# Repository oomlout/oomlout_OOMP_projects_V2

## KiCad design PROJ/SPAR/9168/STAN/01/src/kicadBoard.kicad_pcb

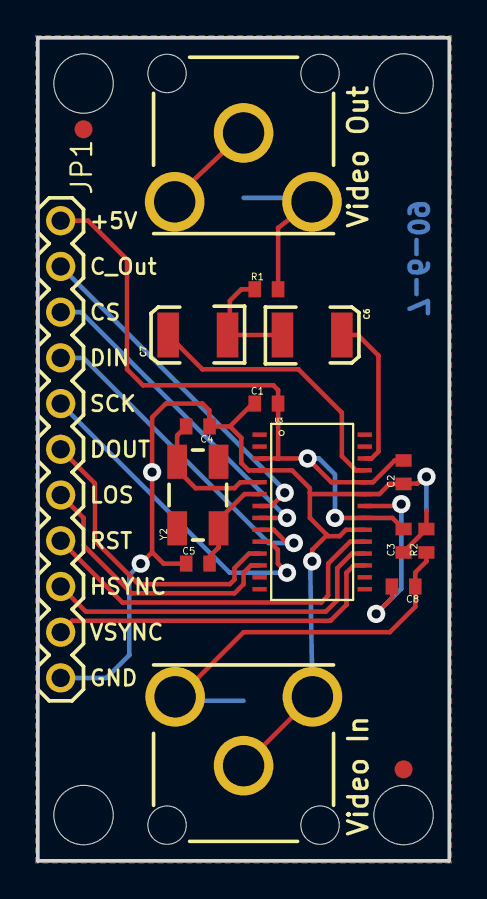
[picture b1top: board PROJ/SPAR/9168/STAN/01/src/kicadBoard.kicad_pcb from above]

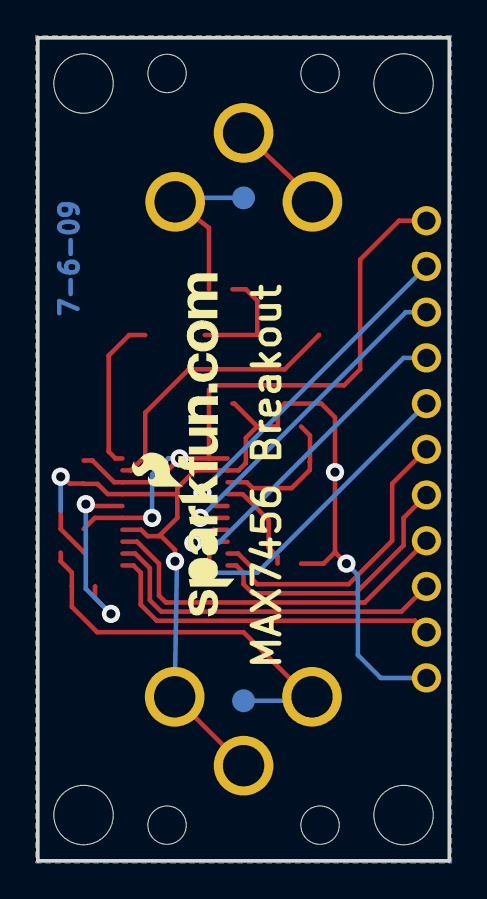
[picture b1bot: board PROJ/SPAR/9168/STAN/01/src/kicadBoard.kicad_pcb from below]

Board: 2 copper layers, 22.9 x 45.7 mm, 24 parts (3 on the bottom side), 19 nets.

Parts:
C1, C2, C3, C8: 0.1uF; C0402
C4, C5: 22pf; C0402
C6, C7: 47uF; EIA3528
J1, J2: POWER_JACKRCA_LOCK; RCA_LOCK
JP1: M11PTH; 1X11
R1, R2: 75; C0402
U3: MAX7456; TSSOP28
U$2, U$12, U$13, U$14: STAND-OFF
U$8: LOGO-SFENEW; SFE-NEW-WEBLOGO
U$9, U$10: FIDUCIAL1X2; FIDUCIAL-1X2
V_IN0: TEST-POINT3X5; PAD.03X.05
V_OUT0: TEST-POINT3X5; PAD.03X.05
Y2: 27MHz; CRYSTAL-SMD-5X3

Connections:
5V: C1.2, C2.2, C3.2, JP1.1, U3.3, U3.21, U3.24
CLKOUT: JP1.2, U3.7
DIN: JP1.4, U3.9
DOUT: JP1.6, U3.11
GND: C1.1, C2.1, C3.1, C4.1, C5.1, J1.BARREL, J1.SPRING, J2.BARREL, J2.SPRING, JP1.11, R2.2, U3.4, U3.20, U3.23
LOS: JP1.7, U3.12
unnamed: C4.2, U3.5, Y2.3
unnamed: C5.2, U3.6, Y2.1
unnamed: C6.C, C7.C, R1.1
unnamed: C7.A, U3.25
unnamed: C6.A, U3.26
unnamed: J1.BREAK, R1.2, V_OUT0.P$1
unnamed: C8.2, U3.22
unnamed: C8.1, J2.BREAK, R2.1, V_IN0.P$1
RESET: JP1.8, U3.19
SCK: JP1.5, U3.10
~CS: JP1.3, U3.8
~HSYNC: JP1.9, U3.18
~VSYNC: JP1.10, U3.17

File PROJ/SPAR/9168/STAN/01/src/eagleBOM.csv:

"Part";"Value";"Device";"Package";"Description";"";
"C1";"0.1uF";"CAP0402";"C0402";"Capacitor";"";
"C2";"0.1uF";"CAP0402";"C0402";"Capacitor";"";
"C3";"0.1uF";"CAP0402";"C0402";"Capacitor";"";
"C4";"22pf";"CAP0402";"C0402";"Capacitor";"";
"C5";"22pf";"CAP0402";"C0402";"Capacitor";"";
"C6";"47uF";"CAP_POL3528";"EIA3528";"Capacitor Polarized";"";
"C7";"47uF";"CAP_POL3528";"EIA3528";"Capacitor Polarized";"";
"C8";"0.1uF";"CAP0402";"C0402";"Capacitor";"";
"J1";"POWER_JACKRCA_LOCK";"POWER_JACKRCA_LOCK";"RCA_LOCK";"Power Jack";"";
"J2";"POWER_JACKRCA_LOCK";"POWER_JACKRCA_LOCK";"RCA_LOCK";"Power Jack";"";
"JP1";"M11PTH";"M11PTH";"1X11";"Header 11";"";
"R1";"75";"RESISTOR0402";"C0402";"Resistor";"";
"R2";"75";"RESISTOR0402";"C0402";"Resistor";"";
"U$2";"STAND-OFF";"STAND-OFF";"STAND-OFF";"Stand Off";"";
"U$8";"LOGO-SFENEW";"LOGO-SFENEW";"SFE-NEW-WEBLOGO";"Spark Fun Electronics PCB Logo";"";
"U$9";"FIDUCIAL1X2";"FIDUCIAL1X2";"FIDUCIAL-1X2";"Fiducial Alignment Points";"";
"U$10";"FIDUCIAL1X2";"FIDUCIAL1X2";"FIDUCIAL-1X2";"Fiducial Alignment Points";"";
"U$12";"STAND-OFF";"STAND-OFF";"STAND-OFF";"Stand Off";"";
"U$13";"STAND-OFF";"STAND-OFF";"STAND-OFF";"Stand Off";"";
"U$14";"STAND-OFF";"STAND-OFF";"STAND-OFF";"Stand Off";"";
"U3";"MAX7456";"MAX7456";"TSSOP28";"";"";
"V_IN";"TEST-POINT3X5";"TEST-POINT3X5";"PAD.03X.05";"";"";
"V_OUT";"TEST-POINT3X5";"TEST-POINT3X5";"PAD.03X.05";"";"";
"Y2";"27MHz";"CRYSTAL5X3";"CRYSTAL-SMD-5X3";"Crystals";"";

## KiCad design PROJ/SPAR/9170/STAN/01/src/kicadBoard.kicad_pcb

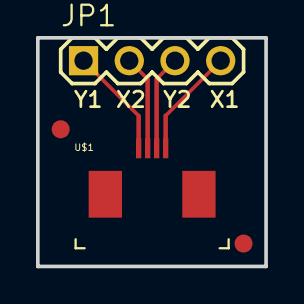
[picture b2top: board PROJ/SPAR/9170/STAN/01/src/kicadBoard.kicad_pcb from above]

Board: 16 copper layers, 12.7 x 12.7 mm, 5 parts (1 on the bottom side), 4 nets.

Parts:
FID1, FID2: FIDUCIAL1X2; FIDUCIAL-1X2
JP1: 1X04
U$1: DS_TOUCH_CONNECTOR
U$2: LOGO-SFESK; SFE-LOGO-FLAME

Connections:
unnamed: JP1.4, U$1.X1
unnamed: JP1.3, U$1.Y2
unnamed: JP1.2, U$1.X2
unnamed: JP1.1, U$1.Y1

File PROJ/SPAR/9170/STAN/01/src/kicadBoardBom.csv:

"Id";"Designator";"Package";"Quantity";"Designation";"Supplier and ref";
1;"JP1";"1X04";1;"";;;
2;"FID2,FID1";"FIDUCIAL-1X2";2;"FIDUCIAL1X2";;;
3;"U$1";"DS_TOUCH_CONNECTOR";1;"DS_TOUCH_CONNECTOR";;;
4;"U$2";"SFE-LOGO-FLAME";1;"LOGO-SFESK";;;

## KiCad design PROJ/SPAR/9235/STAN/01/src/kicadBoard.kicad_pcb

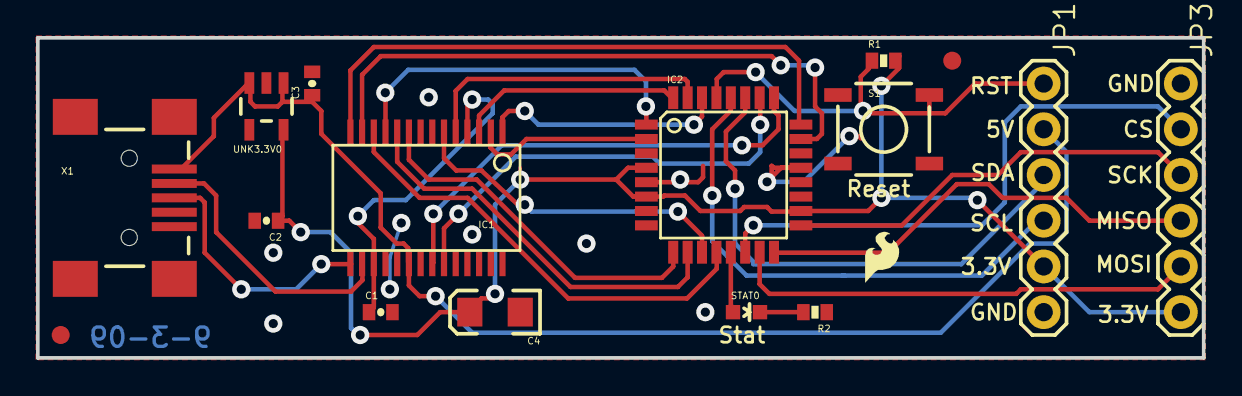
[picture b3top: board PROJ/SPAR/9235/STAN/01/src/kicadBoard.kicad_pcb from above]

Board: 2 copper layers, 64.8 x 17.8 mm, 18 parts (1 on the bottom side), 28 nets.

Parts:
C1, C2: 0.1u; 0402-CAP
C3: 10n; 0402-CAP
C4: 10u; EIA3216
IC1: FT245RL; SSOP28DB
IC2: ATMEGA168; TQFP32-08
JP1, JP3: 1X06
R1: 10k; 0402-RES
R2: 330; 0402-RES
S1: TACTILE_SWITCH_SMD
STAT0: RED; LED-0603
U$3: LOGO-SFENEW; SFE-NEW-WEBLOGO
U$5, U$6: FIDUCIAL1X2; FIDUCIAL-1X2
U$7: LOGO-SFESK; SFE-LOGO-FLAME
UNK3.3V0: V_REG_LDOSMD; SOT23-5
X1: USBSMD; USB-MINIB

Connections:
3.3V: C2.1, C4.A, IC2.4, IC2.6, IC2.18, JP1.5, JP3.6, R1.2, UNK3.3V0.5
CS: IC2.14, JP3.2
GND: C1.2, C2.2, C3.2, C4.C, IC1.7, IC1.18, IC1.21, IC1.25, IC1.26, IC2.3, IC2.5, IC2.21, JP1.6, JP3.1, R2.1, S1.4, UNK3.3V0.2, X1.GND
IOVDD: C1.1, IC1.4, IC1.17
MISO: IC2.16, JP3.4
MOSI: IC2.15, JP3.5
unnamed: IC1.1, IC2.30
unnamed: IC1.5, IC2.31
unnamed: IC1.3, IC2.32
unnamed: IC1.11, IC2.1
unnamed: IC1.2, IC2.2
unnamed: IC1.9, IC2.9
unnamed: IC1.10, IC2.10
unnamed: IC1.6, IC2.11
unnamed: IC1.23, IC2.26
unnamed: IC1.16, X1.D-
unnamed: IC1.15, X1.D+
unnamed: IC1.22, IC2.25
unnamed: IC1.14, IC2.24
unnamed: IC1.13, IC2.23
unnamed: IC1.12, IC2.12
unnamed: IC2.13, STAT0.A
unnamed: R2.2, STAT0.C
RESET: IC2.29, JP1.1, R1.1, S1.2
SCK: IC2.17, JP3.3
SCL: IC2.28, JP1.4
SDA: IC2.27, JP1.3
VUSB: C3.1, IC1.20, JP1.2, UNK3.3V0.1, UNK3.3V0.3, X1.VBUS

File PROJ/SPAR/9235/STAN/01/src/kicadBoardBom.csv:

"Id";"Designator";"Package";"Quantity";"Designation";"Supplier and ref";
1;"R1";"0402-RES";1;"10k";;;
2;"C1,C2";"0402-CAP";2;"0.1u";;;
3;"UNK3.3V0";"SOT23-5";1;"V_REG_LDOSMD";;;
4;"STAT0";"LED-0603";1;"RED";;;
5;"JP3,JP1";"1X06";2;"";;;
6;"U$7";"SFE-LOGO-FLAME";1;"LOGO-SFESK";;;
7;"IC1";"SSOP28DB";1;"FT245RL";;;
8;"U$6,U$5";"FIDUCIAL-1X2";2;"FIDUCIAL1X2";;;
9;"C3";"0402-CAP";1;"10n";;;
10;"R2";"0402-RES";1;"330";;;
11;"C4";"EIA3216";1;"10u";;;
12;"S1";"TACTILE_SWITCH_SMD";1;"";;;
13;"IC2";"TQFP32-08";1;"ATMEGA168";;;
14;"X1";"USB-MINIB";1;"USBSMD";;;
15;"U$3";"SFE-NEW-WEBLOGO";1;"LOGO-SFENEW";;;

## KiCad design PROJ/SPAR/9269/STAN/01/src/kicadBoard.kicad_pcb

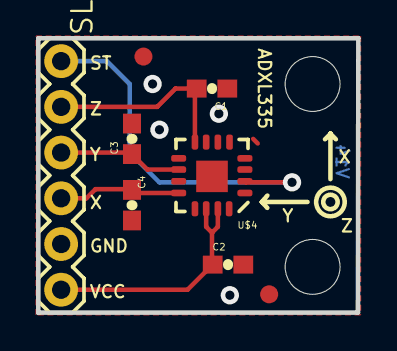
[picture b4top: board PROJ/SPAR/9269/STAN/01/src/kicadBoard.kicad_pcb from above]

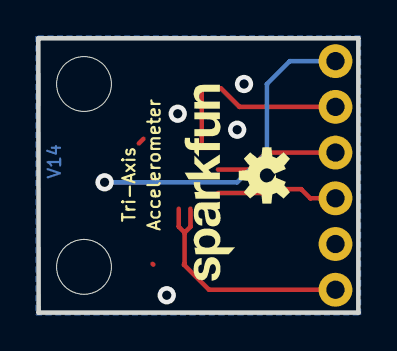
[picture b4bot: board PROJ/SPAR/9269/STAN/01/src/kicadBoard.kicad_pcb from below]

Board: 16 copper layers, 17.8 x 15.2 mm, 12 parts (2 on the bottom side), 6 nets.

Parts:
C1, C2, C3, C4: 0.1uF; 0603-CAP
SL1: 1X06
U$1, U$3: FIDUCIAL1X2; FIDUCIAL-1X2
U$4: ADXL335-PATRICK""; ADXL335-P
U$5: OSHW-LOGO-S
U$6, U$7: STAND-OFF-TIGHT
U$8: SFE_LOGO_NAME_.1

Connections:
GND: C1.1, C2.2, C3.2, C4.2, SL1.5, U$4.3, U$4.5, U$4.6, U$4.7
ST: SL1.1, U$4.2
VCC: C2.1, SL1.6, U$4.14, U$4.15
XOUT: C4.1, SL1.4, U$4.12
YOUT: C3.1, SL1.3, U$4.10
ZOUT: C1.2, SL1.2, U$4.8

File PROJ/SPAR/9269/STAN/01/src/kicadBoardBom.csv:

"Id";"Designator";"Package";"Quantity";"Designation";"Supplier and ref";
1;"C2,C4,C3,C1";"0603-CAP";4;"0.1uF";;;
2;"U$3,U$1";"FIDUCIAL-1X2";2;"FIDUCIAL1X2";;;
3;"U$7,U$6";"STAND-OFF-TIGHT";2;"";;;
4;"U$4";"ADXL335-P";1;"ADXL335-PATRICK""";;;
5;"SL1";"1X06";1;"";;;
6;"U$5";"OSHW-LOGO-S";1;"";;;
7;"U$8";"SFE_LOGO_NAME_.1";1;"";;;

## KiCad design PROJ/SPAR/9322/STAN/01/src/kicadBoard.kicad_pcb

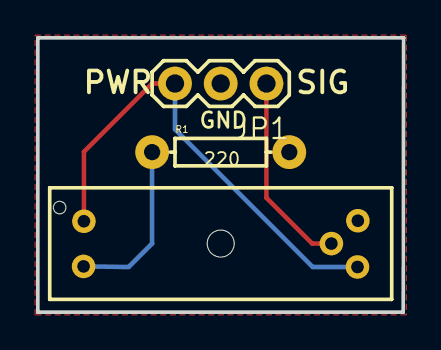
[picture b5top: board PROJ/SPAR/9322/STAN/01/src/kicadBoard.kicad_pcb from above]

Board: 2 copper layers, 20.3 x 15.2 mm, 4 parts (1 on the bottom side), 4 nets.

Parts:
JP1: 1X03
R1: 220; AXIAL-0.3
U1: GP1A57HR
U2: LOGO-SFESK; SFE-LOGO-FLAME

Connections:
GND: JP1.2, R1.P$2, U1.5
unnamed: R1.P$1, U1.2
SIG: JP1.1, U1.4
VCC: JP1.3, U1.1, U1.3

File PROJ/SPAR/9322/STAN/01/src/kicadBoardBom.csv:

"Id";"Designator";"Package";"Quantity";"Designation";"Supplier and ref";
1;"JP1";"1X03";1;"";;;
2;"U1";"GP1A57HR";1;"GP1A57HR";;;
3;"R1";"AXIAL-0.3";1;"220";;;
4;"U2";"SFE-LOGO-FLAME";1;"LOGO-SFESK";;;

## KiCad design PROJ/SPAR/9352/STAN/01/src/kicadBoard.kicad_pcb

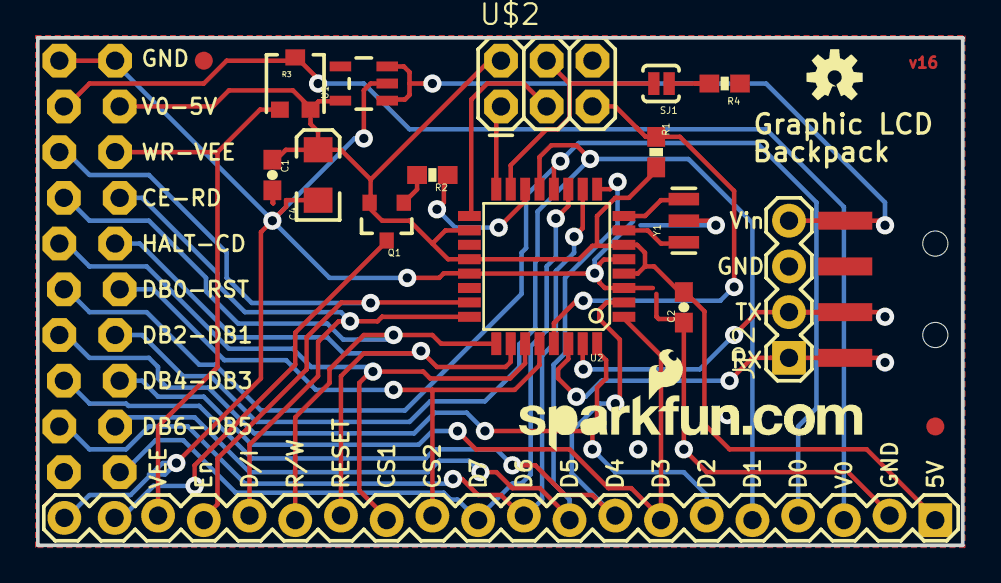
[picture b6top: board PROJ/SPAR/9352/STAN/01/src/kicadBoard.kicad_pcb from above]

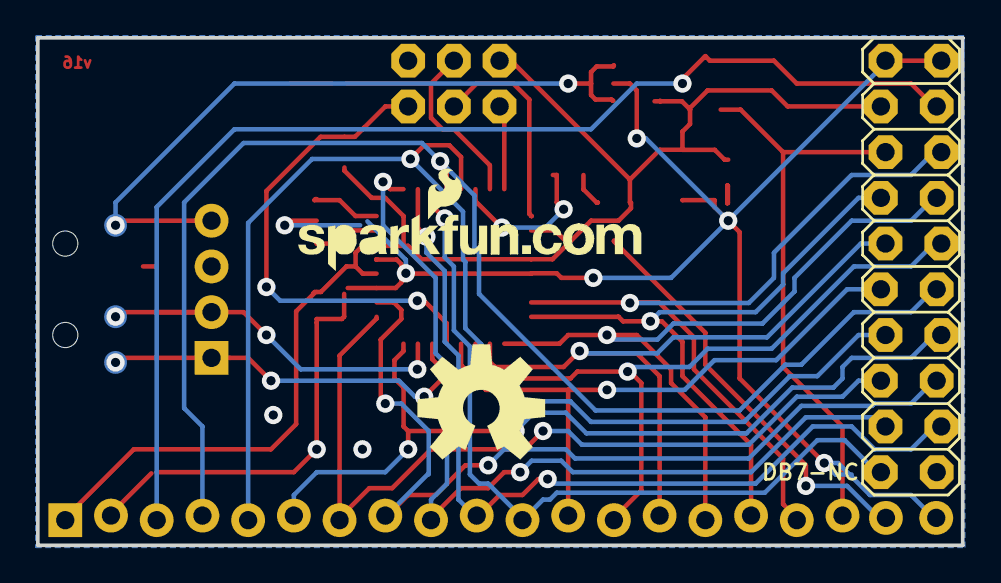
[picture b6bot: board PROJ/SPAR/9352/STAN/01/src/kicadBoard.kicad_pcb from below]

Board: 2 copper layers, 51.4 x 28.2 mm, 27 parts (6 on the bottom side), 31 nets.

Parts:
C1, C2: 0.1uF; 0603-CAP
C4: 10uF; EIA3216
FRAME1: FRAME-LETTER; CREATIVE_COMMONS
JP1: 1X04-SMD
JP2: 1X04
JP3: M20SPECIAL; 1X20_LOCK_SPECIAL
JP4: M10X2SPECIAL; 2X10_LOCK_SPECIAL
LOGO1: OSHW-LOGOL; OSHW-LOGO-L
LOGO2: LOGO-SFENEW; SFE-NEW-WEBLOGO
LOGO3: OSHW-LOGOS; OSHW-LOGO-S
Q1: TRANSISTOR_PNPSMD; SOT23-3
R1: 10K; 0603-RES
R2: 330; 0603-RES
R3: TRIMPOTSMD; TRIMPOT-3MM
R4: 4.7K; 0603-RES
SJ1: SOLDERJUMPERNC2; SJ_2S-NOTRACE
TP1: RXD; PAD.03X.05
TP2: TXD; PAD.03X.05
TP3: VIN; PAD.03X.05
U1: V_REG_LDOSMD; SOT23-5
U2: ATMEGA168; TQFP32-08
U$2: AVR_SPI_PRG_6PTH; 2X3
U$8: LOGO-SFENEW; SFE-NEW-WEBLOGO
U$9, U$10: FIDUCIAL1X2; FIDUCIAL-1X2
Y1: RESONATORSMD; RESONATOR-SMD

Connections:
5V: C1.1, C2.2, C4.A, JP3.1, JP4.3, Q1.2, R1.2, R3.3, U1.5, U2.4, U2.6, U2.18, U2.20, U$2.2
A: JP3.19, Q1.3
BL_EN: R2.1, U2.14
CS1: JP3.13, JP4.10, U2.27
CS2: JP3.12, JP4.11, U2.28
D/I: JP3.16, JP4.7, U2.24
DB0: JP3.4, JP4.12, U2.12
DB1: JP3.5, JP4.13, U2.13
DB2: JP3.6, JP4.14, U2.32
DB3: JP3.7, JP4.15, U2.1
DB4: JP3.8, JP4.16, U2.2
DB5: JP3.9, JP4.17, U2.9
DB6: JP3.10, JP4.18, U2.10
DB7: JP3.11, JP4.19, U2.11
EN: JP3.17, JP4.6, U2.23
GND: C1.2, C2.1, C4.C, JP1.3, JP2.3, JP3.2, JP3.20, JP4.1, JP4.2, R4.1, U1.2, U2.3, U2.5, U2.21, U$2.6, Y1.2
MISO: U2.16, U$2.1
MOSI: SJ1.2, U2.15, U$2.4
unnamed: Q1.1, R2.2
unnamed: U2.7, Y1.1
unnamed: U2.8, Y1.3
unnamed: R4.2, SJ1.1
R/W: JP3.15, JP4.8, U2.25
RESET: JP3.14, JP4.9, U2.26
RST: R1.1, U2.29, U$2.5
RXD: JP1.1, JP2.1, TP1.P$1, U2.30
SCK: U2.17, U$2.3
TXD: JP1.2, JP2.2, TP2.P$1, U2.31
V0: JP3.3, JP4.4, R3.2
VEE: JP3.18, JP4.5, R3.1
VIN: JP1.4, JP2.4, TP3.P$1, U1.1, U1.3

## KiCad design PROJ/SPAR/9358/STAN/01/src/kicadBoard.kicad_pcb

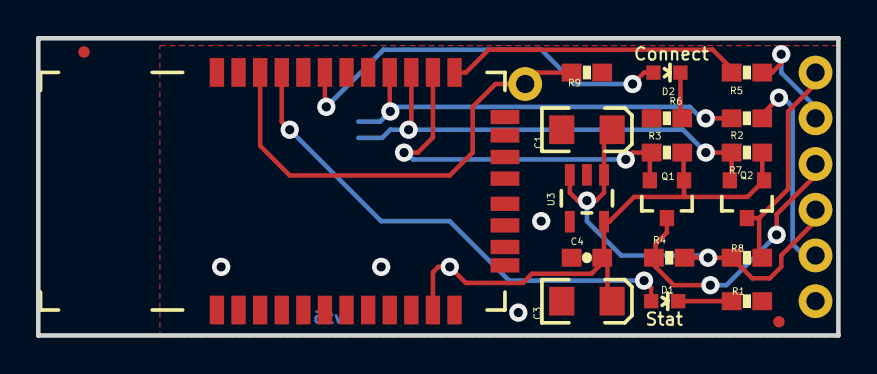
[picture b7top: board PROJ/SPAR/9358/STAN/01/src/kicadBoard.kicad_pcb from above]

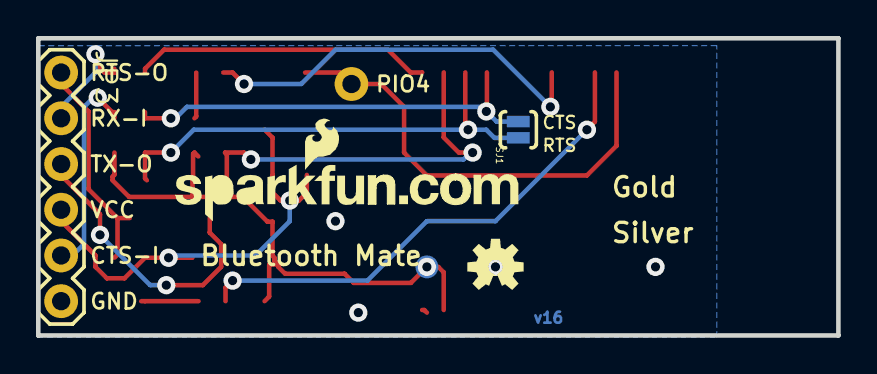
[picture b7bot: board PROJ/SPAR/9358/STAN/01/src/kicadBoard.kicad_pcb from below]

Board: 2 copper layers, 44.5 x 16.5 mm, 28 parts (5 on the bottom side), 16 nets.

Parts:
C1, C3: 10uF; EIA3216
C4: 1uF; 0603-CAP
D1: Red; LED-0603
D2: Green; LED-0603
FRAME1: FRAME-LETTER; CREATIVE_COMMONS
JP1, JP4: FIDUCIAL1X2.5; FIDUCIAL-1X2.5
JP2: M01SMDNS; 1X01NS
JP3: 1X06
LOGO1: OSHW-LOGOS; OSHW-LOGO-S
Q1, Q2: MOSFET-NCHANNELSMD; SOT23-3
R1, R6: 330; 0603-RES
R2, R3, R4, R5, R7, R8, R9: 10K; 0603-RES
SJ1: SOLDERJUMPERNO; SJ_2S-NO
TP1: PAD.03X.05
U1: BLUETOOTH-RN41; RN41
U3: V_REG_LDOSMD; SOT23-5
U$1: LOGO-SFENEW; SFE-NEW-WEBLOGO
U$2: REVISION

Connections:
3.3V: C3.A, C4.1, Q1.1, Q2.1, R3.1, R7.1, TP1.P$1, U1.11, U3.5
CTS: R2.1, SJ1.2, U1.16
CTS_5V: JP3.5, R2.2
D1: D1.C, R1.1
D2: D2.C, R6.1
GND: C1.C, C3.C, C4.2, JP3.6, R1.2, R6.2, R9.1, U1.1, U1.12, U1.28, U1.29, U3.2
unnamed: D1.A, U1.21
unnamed: D2.A, U1.19
PIO4: JP2.1, R9.2, U1.22
RTS: Q2.2, R7.2, SJ1.1, U1.15
RTS_5V: JP3.1, Q2.3, R8.2
RX: R5.1, U1.13
RX_5V: JP3.2, R5.2
TX: Q1.2, R3.2, U1.14
TX_5V: JP3.3, Q1.3, R4.2
VCC: C1.A, JP3.4, R4.1, R8.1, U3.1, U3.3

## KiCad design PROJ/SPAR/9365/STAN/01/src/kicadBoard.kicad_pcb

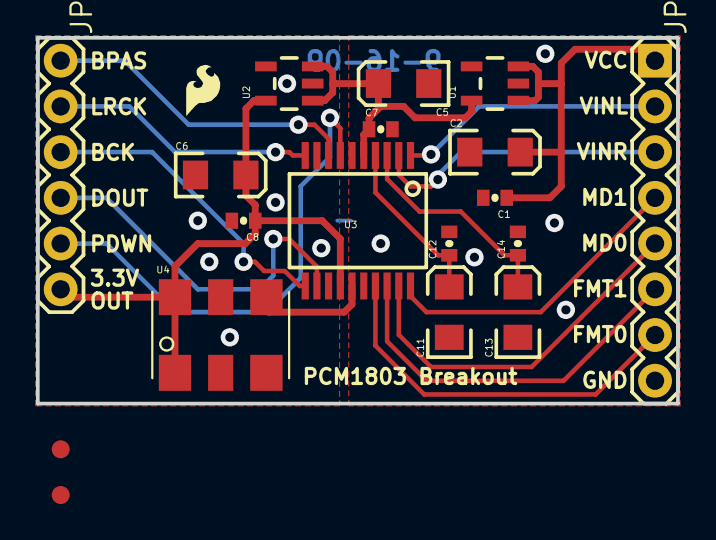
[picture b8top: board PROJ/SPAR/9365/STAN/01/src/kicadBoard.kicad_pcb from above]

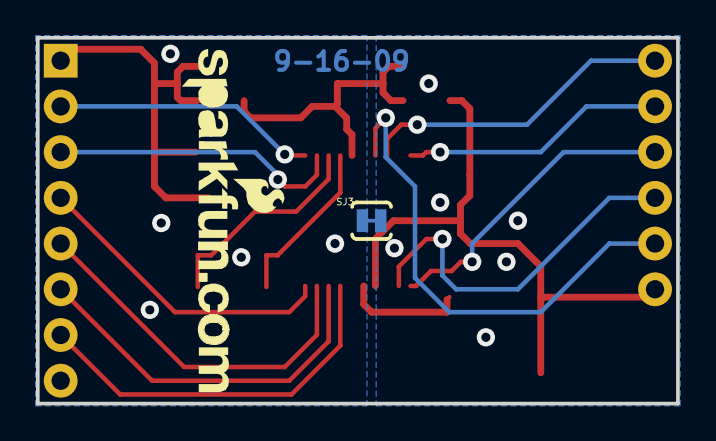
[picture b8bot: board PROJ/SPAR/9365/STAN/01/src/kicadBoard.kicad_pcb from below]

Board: 2 copper layers, 35.6 x 20.3 mm, 21 parts (2 on the bottom side), 19 nets.

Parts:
C1, C7, C8, C12, C14: 0.1uF; 0402-CAP
C2, C5, C6, C11, C13: 10uF; EIA3216
JP1: LOGO-SFESK; SFE-LOGO-FLAME
JP2: 1X06
JP3: 1X08
JP4, JP5: FIDUCIAL1X2; FIDUCIAL-1X2
SJ3: SOLDERJUMPERTRACE; SJ_2S-TRACE
U1: 5V_REG; SOT23-5
U2: 3.3V_REG; SOT23-5
U3: PCM1803SMD; SSOP20
U4: 24.576MHz OSCILLATOR; CRYSTAL-SMD-7.5X5.2-6PIN
U$4: LOGO-SFENEW; SFE-NEW-WEBLOGO

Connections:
3.3V: C6.A, C8.1, JP2.6, U2.5, U3.14, U4.1, U4.4
5V: C5.A, C7.1, U1.5, U2.1, U2.3, U3.5
BCK: JP2.3, U3.11
BPAS: JP2.1, U3.8
DGND: C6.C, C8.2, SJ3.2, U2.2, U3.9, U3.13, U4.2
DOUT: JP2.4, U3.12
FMT0: JP3.7, U3.17
FMT1: JP3.6, U3.18
GND: C1.2, C2.C, C5.C, C7.2, C11.C, C12.2, C13.C, C14.2, JP3.8, SJ3.1, U1.2, U3.6, U3.16
LRCK: JP2.2, U3.10
MD0: JP3.5, U3.19
MD1: JP3.4, U3.20
unnamed: U3.15, U4.3
unnamed: C11.A, C12.1, U3.4
unnamed: C13.A, C14.1, U3.3
PDWN: JP2.5, U3.7
VCC: C1.1, C2.A, JP3.1, U1.1, U1.3
VINL: JP3.2, U3.1
VINR: JP3.3, U3.2

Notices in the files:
parts and their libraries:
RELEASED UNDER THE CREATIVE COMMONS ATTRIBUTION SHARE-ALIKE 3.0 LICENSE
HTTP://CREATIVECOMMONS.ORG/LICENSES/BY-SA/3.0
